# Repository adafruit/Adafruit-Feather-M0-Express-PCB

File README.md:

## Adafruit Feather M0 Express - Designed for CircuitPython - ATSAMD21 Cortex M0 PCB

<a href="http://www.adafruit.com/products/3403"><br/>
Click here to purchase one from the Adafruit shop</a>

PCB files for the Adafruit Feather M0 Express - Designed for CircuitPython - ATSAMD21 Cortex M0. Format is EagleCAD schematic and board layout
* https://www.adafruit.com/product/3403

### Description

We love all our Feathers equally, but this Feather is very special. It's our first Feather that is specifically designed for use with CircuitPython! CircuitPython is our beginner-oriented flavor of MicroPython - and as the name hints at, its a small but full-featured version of the popular Python programming language specifically for use with circuitry and electronics.

Please note, CircuitPython does not come preloaded. See the full guide linked below for instructions on installing it.

That doesn't mean you cant also use it with Arduino IDE! At the Feather M0's heart is an ATSAMD21G18 ARM Cortex M0+ processor, clocked at 48 MHz and at 3.3V logic, the same one used in the new [Arduino Zero](https://www.adafruit.com/products/2843). This chip has a whopping 256K of FLASH (8x more than the Atmega328 or 32u4) and 32K of RAM (16x as much)! This chip comes with built in USB so it has USB-to-Serial program & debug capability built in with no need for an FTDI-like chip.

**Here's some handy specs!**
 * Measures 2.0" x 0.9" x 0.28" (51mm x 23mm x 8mm) without headers soldered in
 * Light as a (large?) feather - 5 grams
 * ATSAMD21G18 @ 48MHz with 3.3V logic/power
 * 256KB of FLASH + 32KB of RAM
 * No EEPROM
 * 32.768 KHz crystal for clock generation & RTC
 * 3.3V regulator with 500mA peak current output
 * USB native support, comes with USB bootloader and serial port debugging
 * You also get tons of pins - 20 GPIO pins
 * Hardware Serial, hardware I2C, hardware SPI support
 * PWM outputs on all pins
 * 6 x 12-bit analog inputs
 * 1 x 10-bit analog ouput (DAC)
 * Built in 100mA lipoly charger with charging status indicator LED
 * Pin #13 red LED for general purpose blinking
 * Power/enable pin
 * 4 mounting holes
 * Reset button

The **Feather M0 Express** uses the extra space left over to add a **Mini NeoPixel, 2 MB SPI Flash** storage and a little prototyping space. You can use the SPI Flash storage like a very tiny hard drive. When used in CircuitPython, the 2 MB flash acts as storage for all your scripts, libraries and files. When used in Arduino, you can read/write files to it, like a little datalogger or SD card, and then with our helper program, access the files over USB.

**Easy reprogramming**: the Feather M0 comes pre-loaded with the [UF2 bootloader](https://learn.adafruit.com/adafruit-feather-m0-express-designed-for-circuit-python-circuitpython/uf2-bootloader), which looks like a USB storage key. Simply drag firmware on to program, no special tools or drivers needed! It can be used to load up CircuitPython, PXT MakeCode or Arduino IDE (it is bossa-compatible)

Comes fully assembled and tested, with the UF2 USB bootloader. We also toss in some header so you can solder it in and plug into a solderless breadboard. 

**Lipoly battery and USB cable not included** (but we do have lots of options in the shop if you'd like!)

[Wanna get started with this fancy new Feather? We have a full guide with details on using it with both Arduino IDE and CircuitPython. The guide also has wiring information, drivers, Fritzing objects, schematics, datasheets and more!](https://learn.adafruit.com/adafruit-feather-m0-express-designed-for-circuit-python-circuitpython)

### License

Adafruit invests time and resources providing this open source design, please support Adafruit and open-source hardware by purchasing products from [Adafruit](https://www.adafruit.com)!

Designed by Limor Fried/Ladyada for Adafruit Industries.

Creative Commons Attribution/Share-Alike, all text above must be included in any redistribution. See license.txt for additional details.

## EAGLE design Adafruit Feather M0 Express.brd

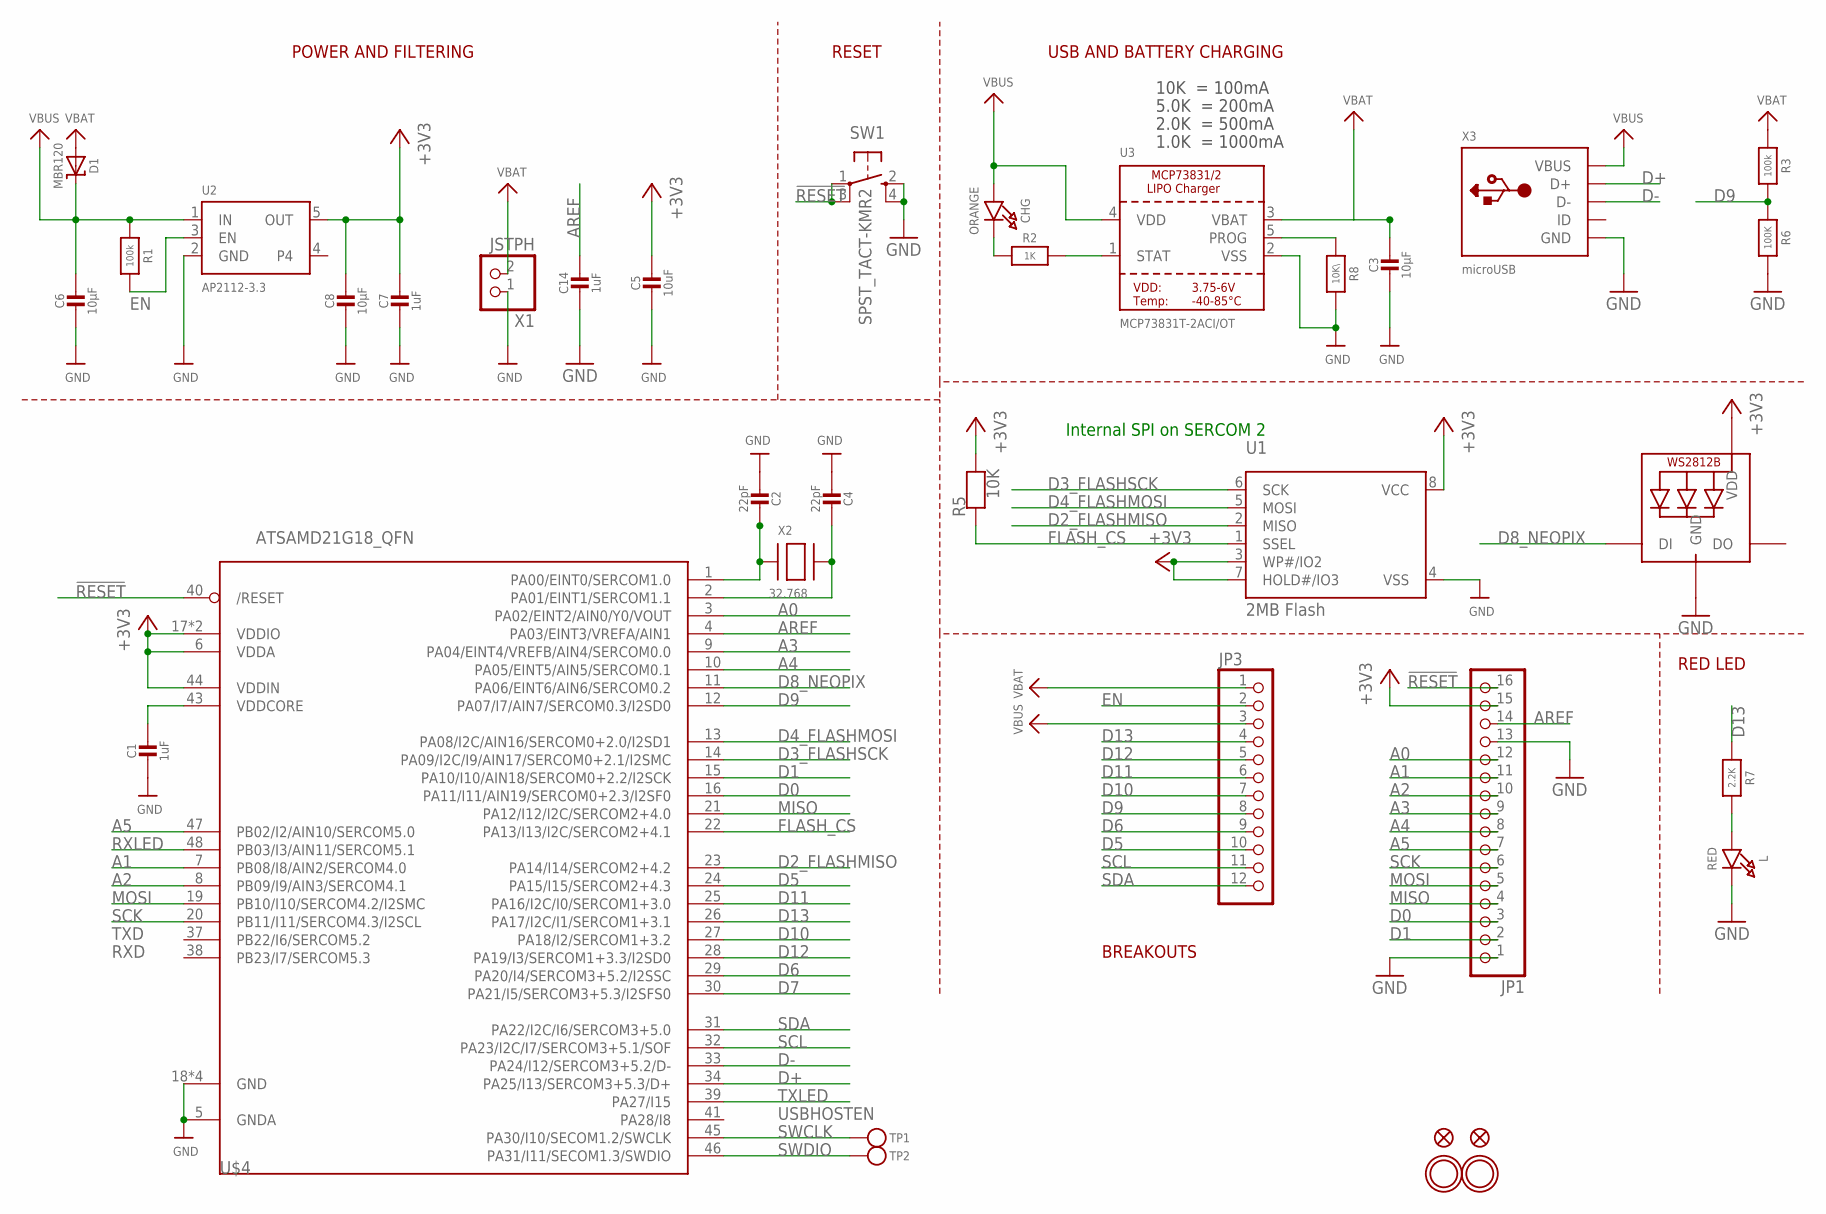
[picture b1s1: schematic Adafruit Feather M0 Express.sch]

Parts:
C1, C7, C14: 1uF; 0603-NO
C2, C4: 22pF; 0603-NO
C3, C6, C8: 10µF; 0805-NO
C5: 10uF; 0805-NO
CHG: ORANGE; CHIPLED_0805_NOOUTLINE
D1: MBR120; SOD-123
JP1: HEADER-1X16ROUND; 1X16_ROUND
JP3: HEADER-1X12; 1X12_ROUND
L: RED; CHIPLED_0805_NOOUTLINE
LED1: WS2812B3535; LED3535
R1, R3: 100k; 0603-NO
R2: 1K; 0603-NO
R5: 10K; 0603-NO
R6: 100K; 0603-NO
R7: 2.2K; 0603-NO
R8: 10K\; 0603-NO
SW1: SPST_TACT-KMR2; KMR2
TP1, TP2: TESTPOINTROUND1.5MM; TESTPOINT_ROUND_1.5MM
U1: 2MB Flash; SOIC8_208MIL
U2: AP2112-3.3; SOT23-5
U3: MCP73831T-2ACI/OT; SOT23-5
U$4: ATSAMD21G18_QFN; TQFN48_7MM
U$31, U$32: MOUNTINGHOLE2.5; MOUNTINGHOLE_2.5_PLATED
U$34, U$35: FIDUCIAL""; FIDUCIAL_1MM
X1: JSTPH; JSTPH2
X2: 32.768; XTAL3215
X3: microUSB; 4UCONN_20329_V2

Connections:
!RESET: JP1.16, SW1.1, SW1.3 (P1), U$4.40 (/RESET)
+3V3: C5.1, C7.1, C8.1, JP1.15, LED1.2 (VDD), R5.2, U1.3 (WP#/IO2), U1.7 (HOLD#/IO3), U1.8 (VCC), U2.5 (OUT), U$4.6 (VDDA), U$4.17 (VDDIO), U$4.36 (VDDIO), U$4.44 (VDDIN)
A0: JP1.12, U$4.3 (PA02/EINT2/AIN0/Y0/VOUT)
A1: JP1.11, U$4.7 (PB08/I8/AIN2/SERCOM4.0)
A2: JP1.10, U$4.8 (PB09/I9/AIN3/SERCOM4.1)
A3: JP1.9, U$4.9 (PA04/EINT4/VREFB/AIN4/SERCOM0.0)
A4: JP1.8, U$4.10 (PA05/EINT5/AIN5/SERCOM0.1)
A5: JP1.7, U$4.47 (PB02/I2/AIN10/SERCOM5.0)
AREF: C14.1, JP1.14, U$4.4 (PA03/EINT3/VREFA/AIN1)
D0: JP1.3, U$4.16 (PA11/I11/AIN19/SERCOM0+2.3/I2SF0)
D1: JP1.2, U$4.15 (PA10/I10/AIN18/SERCOM0+2.2/I2SCK)
D2_FLASHMISO: U1.2 (MISO), U$4.23 (PA14/I14/SERCOM2+4.2)
D3_FLASHSCK: U1.6 (SCK), U$4.14 (PA09/I2C/I9/AIN17/SERCOM0+2.1/I2SMC)
D4_FLASHMOSI: U1.5 (MOSI), U$4.13 (PA08/I2C/AIN16/SERCOM0+2.0/I2SD1)
D5: JP3.10, U$4.24 (PA15/I15/SERCOM2+4.3)
D6: JP3.9, U$4.29 (PA20/I4/SERCOM3+5.2/I2SSC)
D7: U$4.30 (PA21/I5/SERCOM3+5.3/I2SFS0)
D8_NEOPIX: LED1.1 (DI), U$4.11 (PA06/EINT6/AIN6/SERCOM0.2)
D9: JP3.8, R3.2, R6.1, U$4.12 (PA07/I7/AIN7/SERCOM0.3/I2SD0)
D10: JP3.7, U$4.27 (PA18/I2/SERCOM1+3.2)
D11: JP3.6, U$4.25 (PA16/I2C/I0/SERCOM1+3.0)
D12: JP3.5, U$4.28 (PA19/I3/SERCOM1+3.3/I2SD0)
D13: JP3.4, R7.1, U$4.26 (PA17/I2C/I1/SERCOM1+3.1)
D+: U$4.34 (PA25/I13/SERCOM3+5.3/D+), X3.D+
D-: U$4.33 (PA24/I12/SERCOM3+5.2/D-), X3.D-
EN: JP3.2, R1.2, U2.3 (EN)
FLASH_CS: R5.1, U1.1 (SSEL), U$4.22 (PA13/I13/I2C/SERCOM2+4.1)
GND: C1.2, C2.2, C3.2, C4.2, C5.2, C6.2, C7.2, C8.2, C14.2, JP1.1, JP1.13, L.C, LED1.4 (GND), R6.2, R8.2, SW1.2 (S), SW1.4 (S1), U1.4 (VSS), U2.2 (GND), U3.2 (VSS), U$4.5 (GNDA), U$4.18 (GND), U$4.35 (GND), U$4.42 (GND), U$4.THERMAL (GND), X1.1, X3.BASE@1 (GND), X3.BASE@2 (GND), X3.GND, X3.SPRT@1 (GND), X3.SPRT@2 (GND), X3.SPRT@3 (GND), X3.SPRT@4 (GND)
MISO: JP1.4, U$4.21 (PA12/I12/I2C/SERCOM2+4.0)
MOSI: JP1.5, U$4.19 (PB10/I10/SERCOM4.2/I2SMC)
unnamed: CHG.C, R2.1
unnamed: L.A, R7.2
unnamed: R2.2, U3.1 (STAT)
unnamed: R8.1, U3.5 (PROG)
unnamed: C2.1, U$4.1 (PA00/EINT0/SERCOM1.0), X2.P$1
unnamed: C4.1, U$4.2 (PA01/EINT1/SERCOM1.1), X2.P$2
RXLED: U$4.48 (PB03/I3/AIN11/SERCOM5.1)
SCK: JP1.6, U$4.20 (PB11/I11/SERCOM4.3/I2SCL)
SCL: JP3.11, U$4.32 (PA23/I2C/I7/SERCOM3+5.1/SOF)
SDA: JP3.12, U$4.31 (PA22/I2C/I6/SERCOM3+5.0)
SWCLK: TP1.P$1, U$4.45 (PA30/I10/SECOM1.2/SWCLK)
SWDIO: TP2.P$1, U$4.46 (PA31/I11/SECOM1.3/SWDIO)
TXLED: U$4.39 (PA27/I15)
VBAT: C3.1, D1.A, JP3.1, R3.1, U3.3 (VBAT), X1.2
VBUS: C6.1, CHG.A, D1.C, JP3.3, R1.1, U2.1 (IN), U3.4 (VDD), X3.VBUS
VDDCORE: C1.1, U$4.43 (VDDCORE)

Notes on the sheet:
POWER AND FILTERING
RESET
10K = 100mA
5.0K = 200mA
2.0K = 500mA
1.0K = 1000mA
USBHOSTEN
TXD
RXD
USB AND BATTERY CHARGING
BREAKOUTS
RED LED
Internal SPI on SERCOM 2

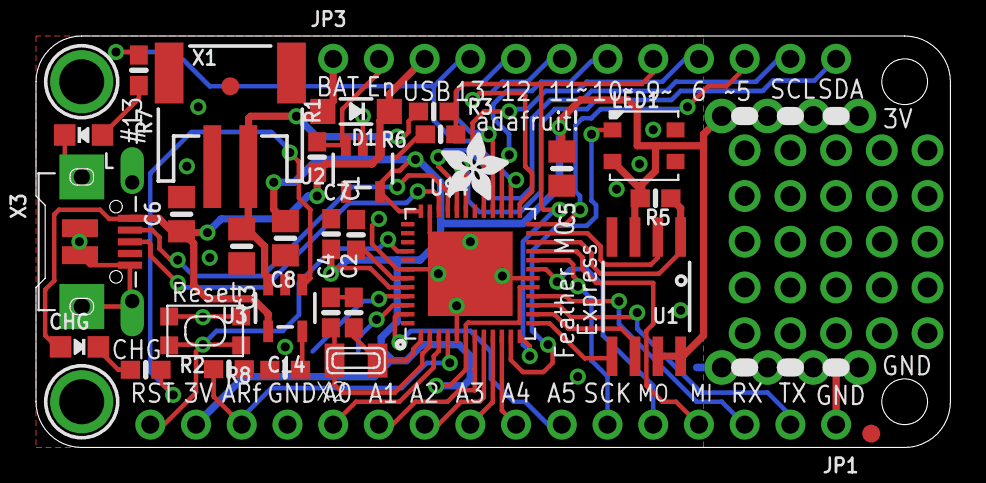
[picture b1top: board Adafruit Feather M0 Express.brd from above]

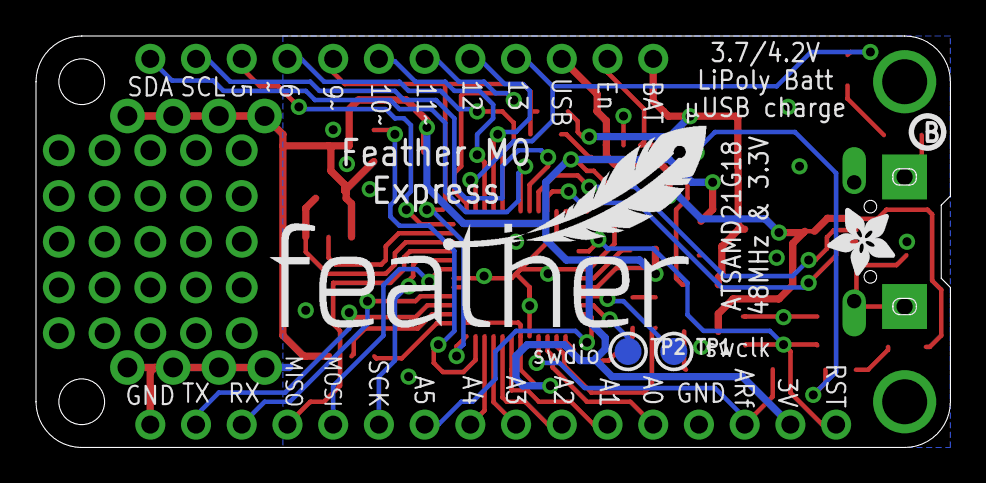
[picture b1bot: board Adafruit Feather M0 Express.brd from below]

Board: 2 copper layers, 50.8 x 22.9 mm, 40 parts (5 on the bottom side), 43 nets.

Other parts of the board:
U$7, U$12: ADAFRUIT_3.5MM
U$9: FEATHERLOGO
U$13: PCBFEAT-REV-040

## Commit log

2017-03-31 init
2019-01-04 Add schematic PDF
2019-07-17 updated to use cookiecutter for pcb repos
2021-05-18 Add pinout PDF

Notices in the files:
parts and their libraries:
microbuilder: This work is placed in the public domain, and may be freely used for commercial and non-commercial work with the following conditions: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
